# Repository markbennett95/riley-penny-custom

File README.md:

# Custom Dual OD - Riley Penney

Custom dual drive in a 1590BB - Called the "Chinook Overdrive", it features a Zendrive on one side, and a modified BD-2 on the the other.

## v1.0.0-build
1590BB encl. Works with `1590BB-2` of the [Dual Effect Order Switching Board](https://github.com/markbennett95/dual-effect-order-switching-board). Zendrive schematic is unchanged, using the "version" switch and a DG412. The BD-2 is heavily modified from the original; It features an active baxendall 2-band tone stack, and a gyrator-based 3-way "Mids" switch. Some zener diodes were added in the feedback path of the second gain stage, which went a long ways in cleaning up some of the fizziness inherent in the original version.

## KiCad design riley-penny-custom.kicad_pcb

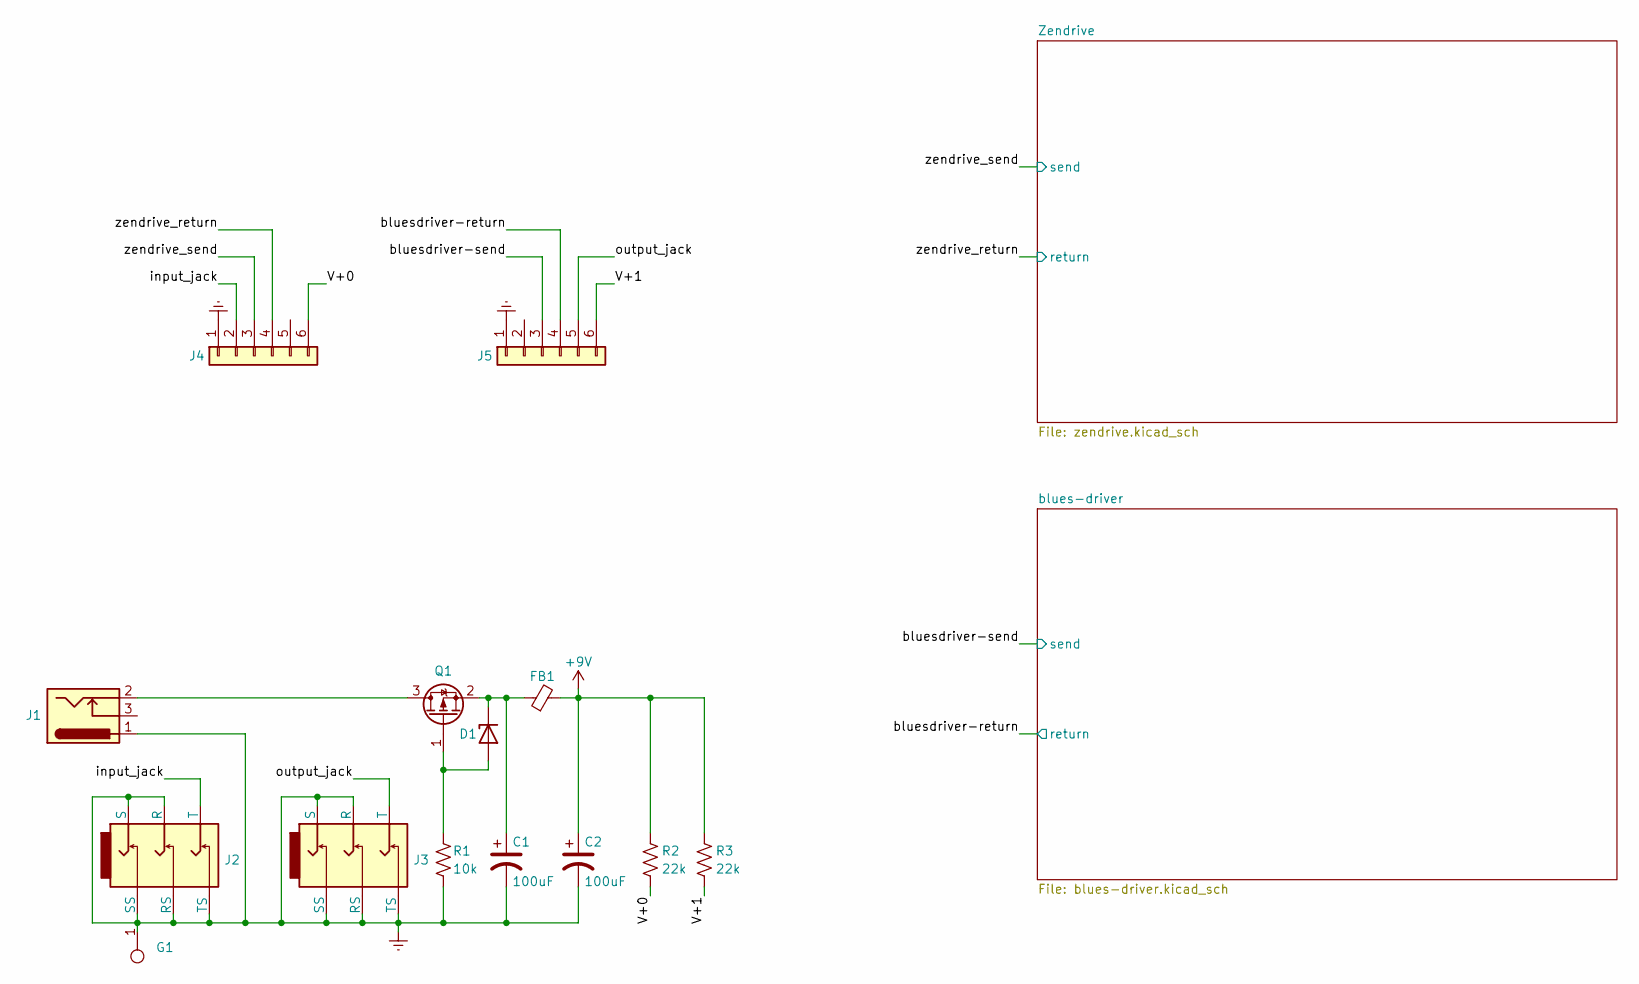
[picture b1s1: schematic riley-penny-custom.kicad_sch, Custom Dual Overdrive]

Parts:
C1, C2: 100uF; CP_Radial_D6.3mm_P2.50mm
D1: 9V1 Zener; D_SOD-323_HandSoldering
FB1: FerriteBead_Small; L_0805_2012Metric_Pad1.15x1.40mm_HandSolder
G1: GNDSpring; Keystone_628
J1: Barrel_Jack_Switch; DC_Jack_DC005
J2, J3: AudioJack_TRS; Rean_NYS215
J4, J5: Conn_01x06; Pin_Header_Straight_1x06_Pitch2.54mm
Q1: Q_PMOS_GSD; SOT-23_Handsoldering
R1: 10k; R_0805_2012Metric_Pad1.20x1.40mm_HandSolder
R2, R3: 22k; R_0805_2012Metric_Pad1.20x1.40mm_HandSolder

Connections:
+9V: C2.1, FB1.2, R2.2, R3.2; also elsewhere on the board
/V+0: J4.6, R2.1
/V+1: J5.6, R3.1
/bluesdriver-return: J5.4; also elsewhere on the board
/bluesdriver-send: J5.3; also elsewhere on the board
/input_jack: J2.1 (T), J4.2
/output_jack: J3.1 (T), J5.5
/zendrive_return: J4.4; also elsewhere on the board
/zendrive_send: J4.3; also elsewhere on the board
Earth: C1.2, C2.2, G1.1, J1.1, J2.2 (R), J2.3 (S), J2.4 (TS), J2.5 (RS), J2.6 (SS), J3.2 (R), J3.3 (S), J3.4 (TS), J3.5 (RS), J3.6 (SS), J4.1, J5.1, R1.1; also elsewhere on the board
unnamed: D1.2 (A), Q1.1 (G), R1.2
unnamed: C1.1, D1.1 (K), FB1.1, Q1.2 (S)
unnamed: J1.2, Q1.3 (D)

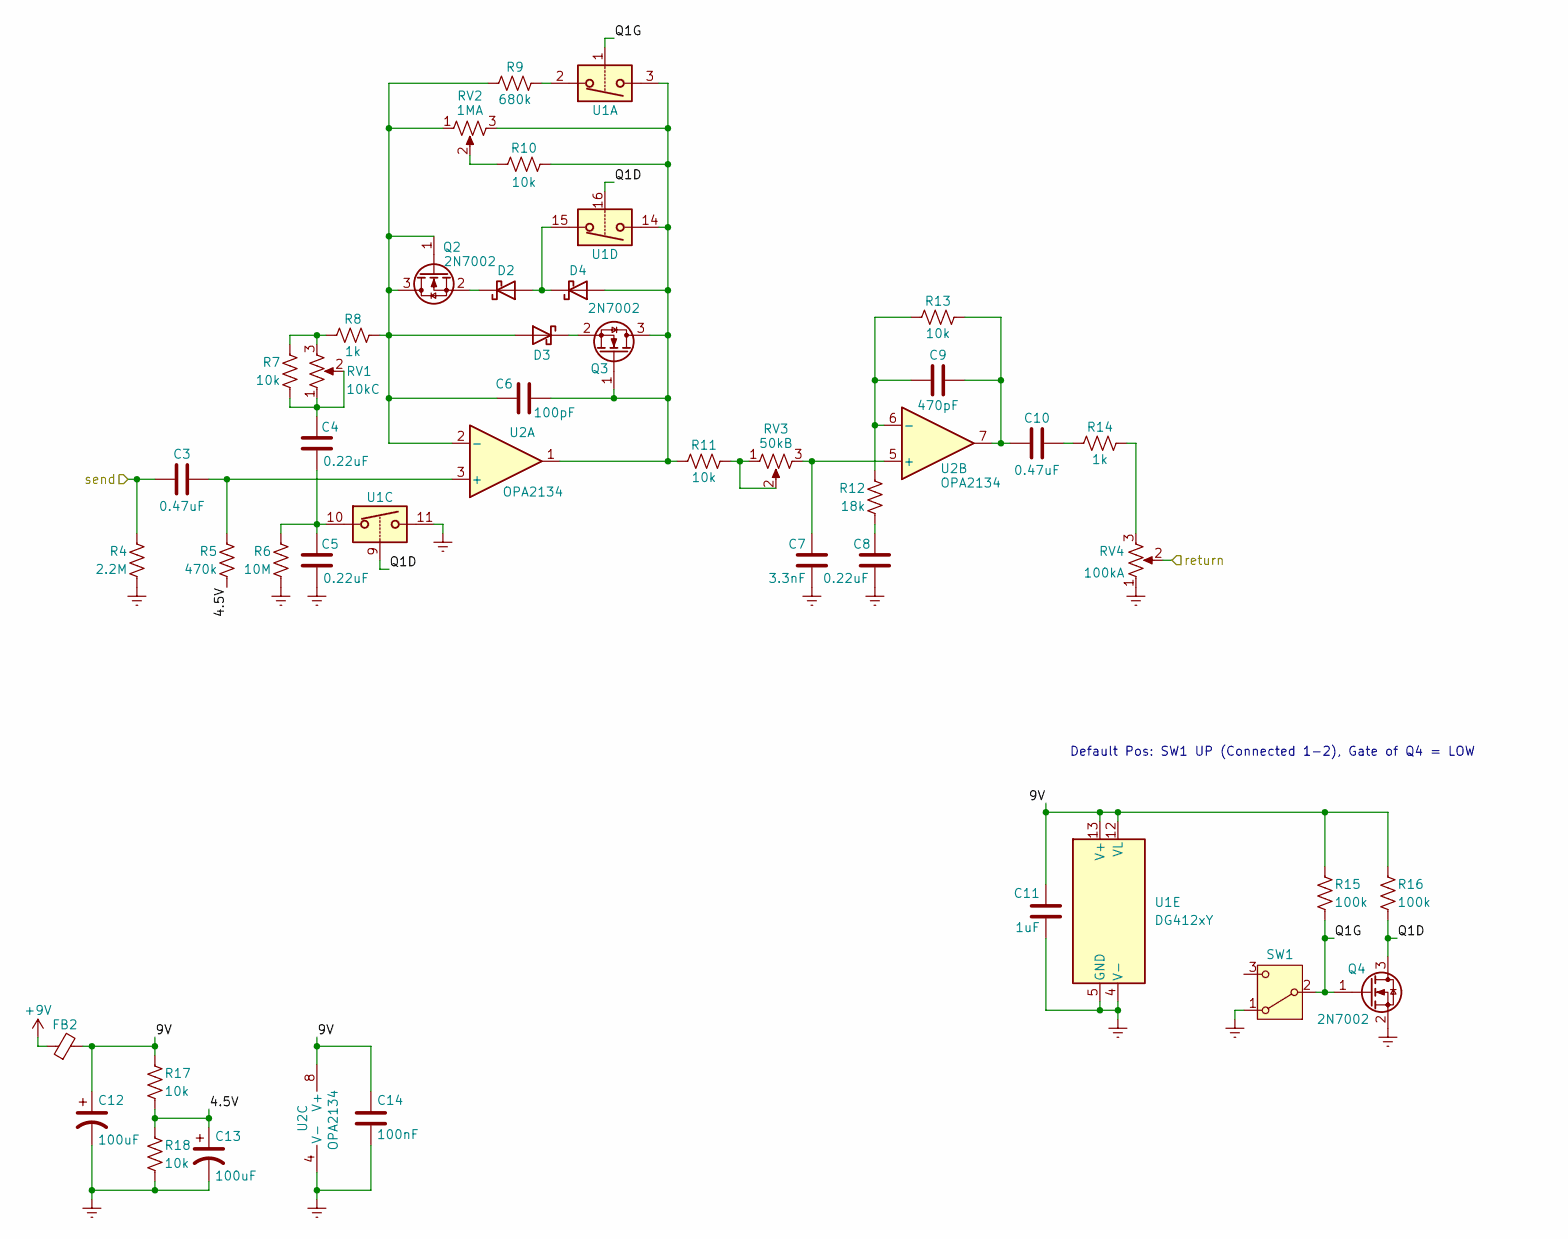
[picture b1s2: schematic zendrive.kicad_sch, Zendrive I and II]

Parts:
C3, C10: 0.47uF; C_Film_L7.2mm_W3.5mm_P5.00mm
C4, C5, C8: 0.22uF; C_Film_L7.2mm_W3.5mm_P5.00mm
C6: 100pF; C_0603_1608Metric_Pad1.08x0.95mm_HandSolder
C7: 3.3nF; C_Film_L7.2mm_W2.5mm_P5.00mm
C9: 470pF; C_0603_1608Metric_Pad1.08x0.95mm_HandSolder
C11: 1uF; C_0805_2012Metric_Pad1.18x1.45mm_HandSolder
C12, C13: 100uF; CP_Radial_D6.3mm_P2.50mm
C14: 100nF; C_0603_1608Metric_Pad1.08x0.95mm_HandSolder
D2, D3, D4: 1N5711; Diode_DO-35_P5.00mm
FB2: FerriteBead_Small; L_0805_2012Metric_Pad1.15x1.40mm_HandSolder
Q2, Q3, Q4: 2N7002; SOT-23_Handsoldering
R4: 2.2M; R_L3.6mm_D1.6mm_P5.00mm_Horizontal
R5: 470k; R_L3.6mm_D1.6mm_P5.00mm_Horizontal
R6: 10M; R_0805_2012Metric_Pad1.20x1.40mm_HandSolder
R7, R10, R11, R13: 10k; R_L3.6mm_D1.6mm_P5.00mm_Horizontal
R8, R14: 1k; R_L3.6mm_D1.6mm_P5.00mm_Horizontal
R9: 680k; R_L3.6mm_D1.6mm_P5.00mm_Horizontal
R12: 18k; R_L3.6mm_D1.6mm_P5.00mm_Horizontal
R15, R16: 100k; R_L3.6mm_D1.6mm_P5.00mm_Horizontal
R17, R18: 10k; R_0805_2012Metric_Pad1.20x1.40mm_HandSolder
RV1: 10kC; R_POT
RV2: 1MA; R_POT
RV3: 50kB; R_POT
RV4: 100kA; R_POT
SW1: SW_SPDT; SW_Toggle_SPDT_SolderLug
U1: DG412xY; SOIC-16_3.9x9.9mm_P1.27mm
U2: OPA2134; SOIC-8_3.9x4.9mm_P1.27mm

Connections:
+9V: FB2.1; also elsewhere on the board
/Zendrive/4.5V: C13.1, R5.1, R17.1, R18.2
/Zendrive/9V: C11.1, C12.1, C14.1, FB2.2, R15.2, R16.2, R17.2, U1.12 (VL), U1.13 (V+), U2.8 (V+)
/Zendrive/Q1D: Q4.3 (D), R16.1, U1.9, U1.16
/Zendrive/Q1G: Q4.1 (G), R15.1, SW1.2 (B), U1.1
/zendrive_return: RV4.2; also elsewhere on the board
/zendrive_send: C3.1, R4.2; also elsewhere on the board
Earth: C5.1, C7.2, C8.1, C11.2, C12.2, C13.2, C14.2, Q4.2 (S), R4.1, R6.1, R18.1, RV4.1, SW1.1 (A), U1.4 (V-), U1.5 (GND), U1.11, U2.4 (V-); also elsewhere on the board
unnamed: C4.1, C5.2, R6.2, U1.10
unnamed: C4.2, R7.1, RV1.1, RV1.2
unnamed: C8.2, R12.1
unnamed: C9.2, C10.1, R13.2, U2.7
unnamed: C10.2, R14.1
unnamed: D2.2 (A), D4.1 (K), U1.15
unnamed: D2.1 (K), Q2.2 (S)
unnamed: C6.1, D3.2 (A), Q2.1 (G), Q2.3 (D), R8.2, R9.1, RV2.1, U2.2 (-)
unnamed: D3.1 (K), Q3.2 (S)
unnamed: C6.2, D4.2 (A), Q3.1 (G), Q3.3 (D), R10.2, R11.1, RV2.3, U1.3, U1.14, U2.1
unnamed: R7.2, R8.1, RV1.3
unnamed: R9.2, U1.2
unnamed: R10.1, RV2.2
unnamed: R11.2, RV3.1, RV3.2
unnamed: R14.2, RV4.3
unnamed: C3.2, R5.2, U2.3 (+)
unnamed: C7.1, RV3.3, U2.5 (+)
unnamed: C9.1, R12.2, R13.1, U2.6 (-)

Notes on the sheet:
Default Pos: SW1 UP (Connected 1-2), Gate of Q4 = LOW

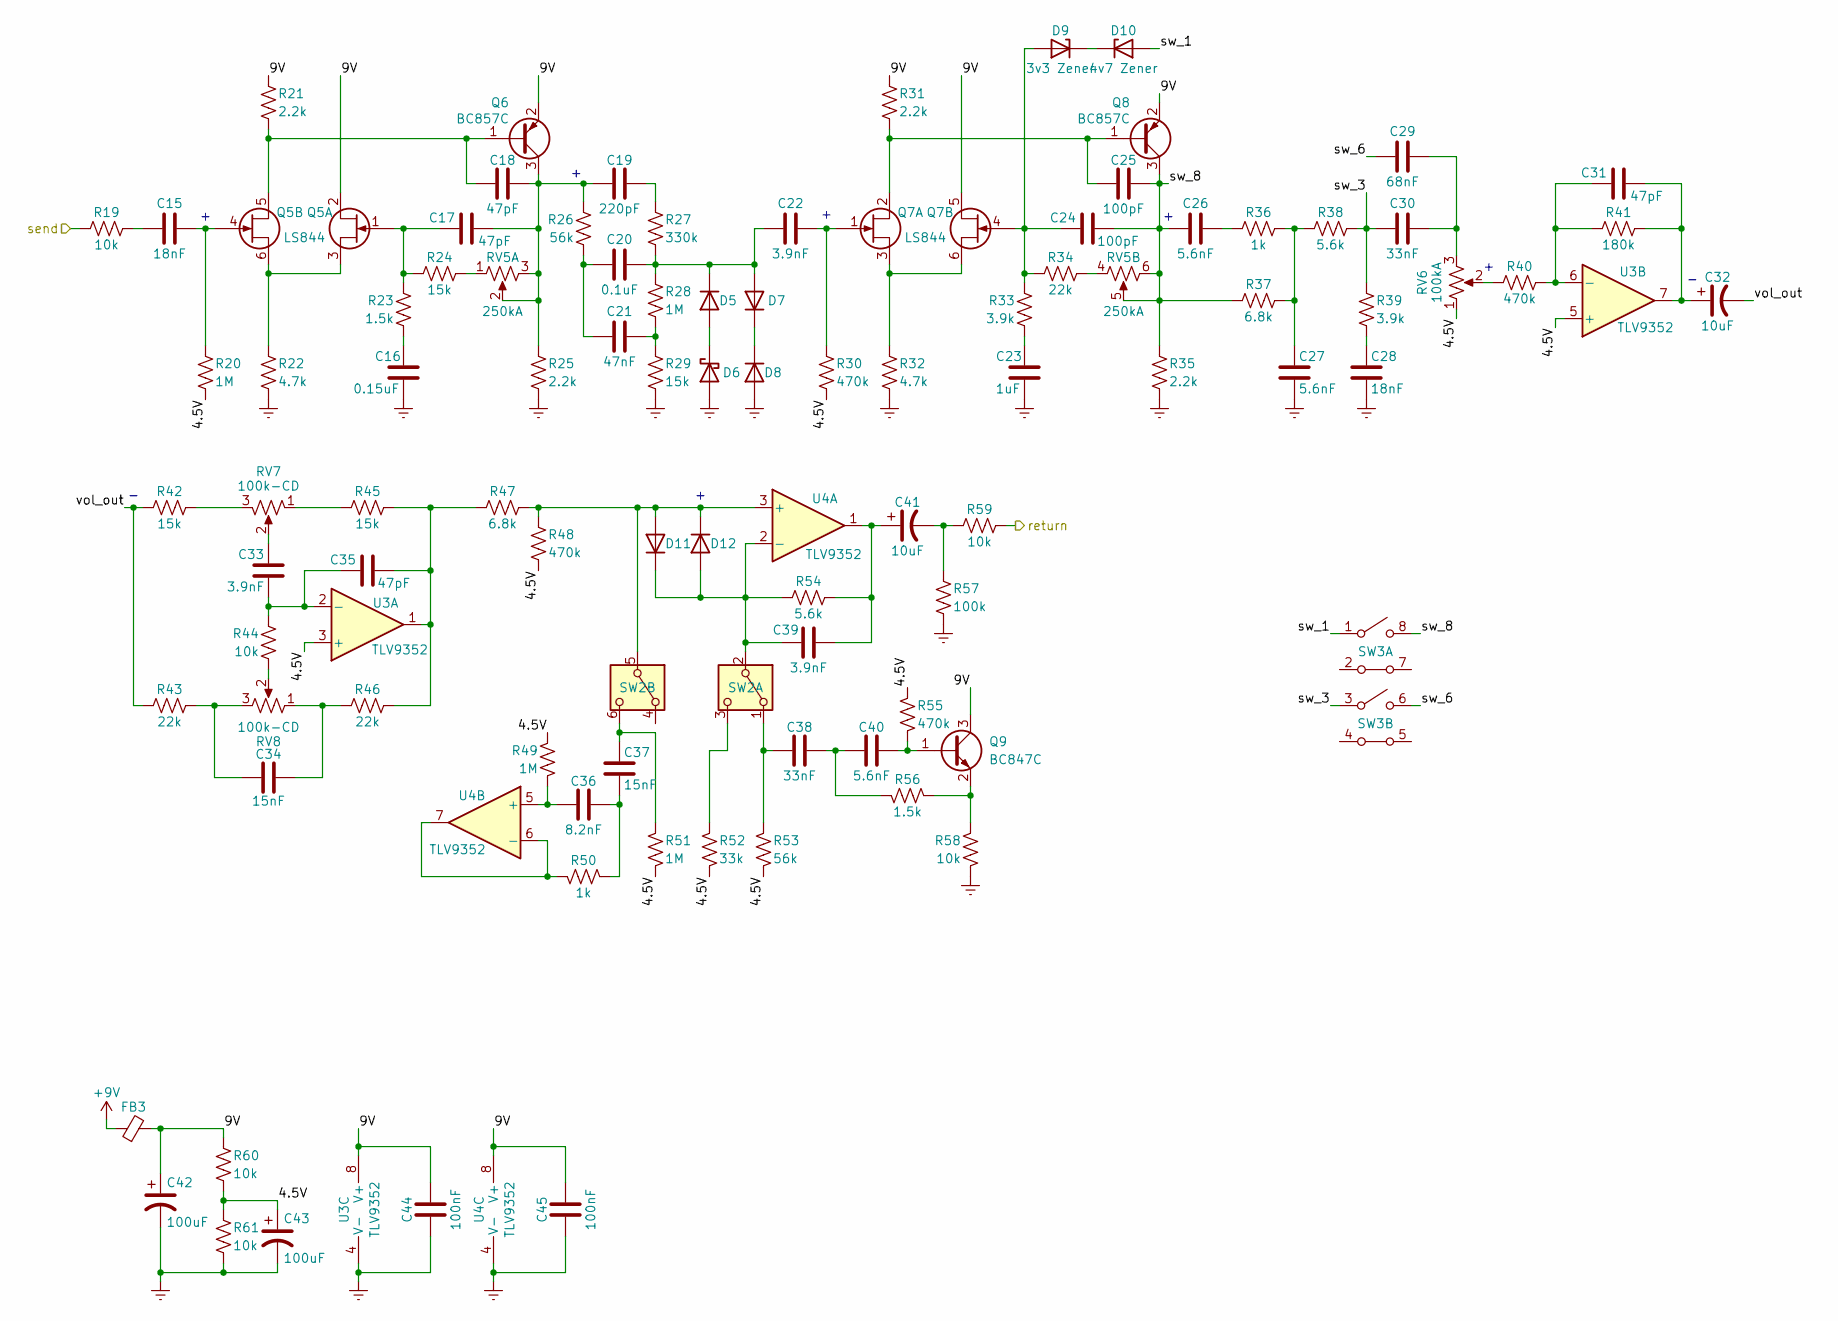
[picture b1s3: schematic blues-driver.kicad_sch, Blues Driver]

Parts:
C15, C28: 18nF; C_Film_L7.2mm_W2.5mm_P5.00mm
C16: 0.15uF; C_Film_L7.2mm_W3.5mm_P5.00mm
C17, C18, C31, C35: 47pF; C_0603_1608Metric_Pad1.08x0.95mm_HandSolder
C19: 220pF; C_Ceramic_L4.0mm_W2.5mm_P2.50mm
C20: 0.1uF; C_Film_L7.2mm_W2.5mm_P5.00mm
C21: 47nF; C_Film_L7.2mm_W2.5mm_P5.00mm
C22, C33, C39: 3.9nF; C_Film_L7.2mm_W2.5mm_P5.00mm
C23: 1uF; C_Film_L7.2mm_W3.5mm_P5.00mm
C24, C25: 100pF; C_0603_1608Metric_Pad1.08x0.95mm_HandSolder
C26, C27, C40: 5.6nF; C_Film_L7.2mm_W2.5mm_P5.00mm
C29: 68nF; C_Film_L7.2mm_W2.5mm_P5.00mm
C30, C38: 33nF; C_Film_L7.2mm_W2.5mm_P5.00mm
C32, C41: 10uF; CP_Radial_D4.0mm_P1.50mm
C34, C37: 15nF; C_Film_L7.2mm_W2.5mm_P5.00mm
C36: 8.2nF; C_Film_L7.2mm_W2.5mm_P5.00mm
C42, C43: 100uF; CP_Radial_D6.3mm_P2.50mm
C44, C45: 100nF; C_0603_1608Metric_Pad1.08x0.95mm_HandSolder
D5, D7, D8, D11, D12: 1N4148; Diode_DO-35_P5.00mm
D6: 1N5711; Diode_DO-35_P5.00mm
D9: 3v3 Zener; Diode_Zener_DO-35_P5.00mm
D10: 4v7 Zener; Diode_Zener_DO-35_P5.00mm
FB3: FerriteBead_Small; L_0805_2012Metric_Pad1.15x1.40mm_HandSolder
Q5, Q7: LS844; SOT-23-6_Handsoldering
Q6, Q8: BC857C; SOT-23_Handsoldering
Q9: BC847C; SOT-23_Handsoldering
R19, R44, R58, R59: 10k; R_L3.6mm_D1.6mm_P5.00mm_Horizontal
R20, R49, R51: 1M; R_0805_2012Metric_Pad1.20x1.40mm_HandSolder
R21, R25, R31, R35: 2.2k; R_0603_1608Metric_Pad0.98x0.95mm_HandSolder
R22, R32: 4.7k; R_0603_1608Metric_Pad0.98x0.95mm_HandSolder
R23, R56: 1.5k; R_L3.6mm_D1.6mm_P5.00mm_Horizontal
R24, R29, R42, R45: 15k; R_L3.6mm_D1.6mm_P5.00mm_Horizontal
R26, R53: 56k; R_L3.6mm_D1.6mm_P5.00mm_Horizontal
R27: 330k; R_L3.6mm_D1.6mm_P5.00mm_Horizontal
R28: 1M; R_L3.6mm_D1.6mm_P5.00mm_Horizontal
R30, R40, R48, R55: 470k; R_L3.6mm_D1.6mm_P5.00mm_Horizontal
R33, R39: 3.9k; R_L3.6mm_D1.6mm_P5.00mm_Horizontal
R34, R43, R46: 22k; R_L3.6mm_D1.6mm_P5.00mm_Horizontal
R36, R50: 1k; R_L3.6mm_D1.6mm_P5.00mm_Horizontal
R37, R47: 6.8k; R_L3.6mm_D1.6mm_P5.00mm_Horizontal
R38, R54: 5.6k; R_L3.6mm_D1.6mm_P5.00mm_Horizontal
R41: 180k; R_L3.6mm_D1.6mm_P5.00mm_Horizontal
R52: 33k; R_0805_2012Metric_Pad1.20x1.40mm_HandSolder
R57: 100k; R_L3.6mm_D1.6mm_P5.00mm_Horizontal
R60, R61: 10k; R_0805_2012Metric_Pad1.20x1.40mm_HandSolder
RV5: 250kA; R_POT_DUAL
RV6: 100kA; R_POT
RV7, RV8: 100k-CD; R_POT
SW2: SW_DPDT_x2; SW_Toggle_DPDT_SolderLug
SW3: SW_DIP_SPDT_2pos; DIP-8_W7.62mm_Socket
U3, U4: TLV9352; SOIC-8_3.9x4.9mm_P1.27mm

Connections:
+9V: FB3.1; also elsewhere on the board
/blues-driver/4.5V: C43.1, R20.1, R30.1, R48.1, R49.2, R51.1, R52.1, R53.1, R55.2, R60.1, R61.2, RV6.1, U3.3 (+), U3.5 (+)
/blues-driver/9V: C42.1, C44.1, C45.1, FB3.2, Q5.2 (D1), Q6.2 (E), Q7.5 (D2), Q8.2 (E), Q9.3 (C), R21.2, R31.2, R60.2, U3.8 (V+), U4.8 (V+)
/blues-driver/sw_1: D10.2 (A), SW3.1 (C)
/blues-driver/sw_3: C30.1, R38.2, R39.2, SW3.3 (C)
/blues-driver/sw_6: C29.1, SW3.6 (A)
/blues-driver/sw_8: C24.2, C25.2, C26.1, Q8.3 (C), R35.2, R37.1, RV5.5, RV5.6, SW3.8 (A)
/blues-driver/vol_out: C32.2, R42.1, R43.1
/bluesdriver-return: R59.2; also elsewhere on the board
/bluesdriver-send: R19.1; also elsewhere on the board
Earth: C16.2, C23.2, C27.1, C28.1, C42.2, C43.2, C44.2, C45.2, D6.2 (A), D8.2 (A), R22.1, R25.1, R29.1, R32.1, R35.1, R57.1, R58.1, R61.1, U3.4 (V-), U4.4 (V-); also elsewhere on the board
unnamed: C15.1, R19.2
unnamed: C16.1, R23.1
unnamed: C19.2, R27.2
unnamed: C20.1, C21.1, R26.1
unnamed: C21.2, R28.1, R29.2
unnamed: C23.1, R33.1
unnamed: C26.2, R36.1
unnamed: C27.2, R36.2, R37.2, R38.1
unnamed: C28.2, R39.1
unnamed: C29.2, C30.2, RV6.3
unnamed: C31.2, C32.1, R41.2, U3.7
unnamed: C33.2, RV7.2
unnamed: C34.1, R46.1, RV8.1
unnamed: C34.2, R43.2, RV8.3
unnamed: C35.2, R45.2, R46.2, R47.1, U3.1
unnamed: C36.2, C37.1, R50.1
unnamed: C38.2, C40.1, R56.2
unnamed: C39.2, C41.1, R54.2, U4.1
unnamed: C41.2, R57.2, R59.1
unnamed: D5.2 (A), D6.1 (K)
unnamed: C20.2, C22.1, D5.1 (K), D7.2 (A), R27.1, R28.2
unnamed: D7.1 (K), D8.1 (K)
unnamed: C24.1, D9.2 (A), Q7.4 (G1), R33.2, R34.1
unnamed: D9.1 (K), D10.1 (K)
unnamed: D11.2 (A), D12.1 (K), R47.2, R48.2, SW2.5 (B), U4.3 (+)
unnamed: C39.1, D11.1 (K), D12.2 (A), R54.1, SW2.2 (B), U4.2 (-)
unnamed: C17.1, Q5.1 (G1), R23.2, R24.1
unnamed: Q5.3 (S1), Q5.6 (S1), R22.2
unnamed: C18.1, Q5.5 (D2), Q6.1 (B), R21.1
unnamed: C15.2, Q5.4 (G1), R20.2
unnamed: C17.2, C18.2, C19.1, Q6.3 (C), R25.2, R26.2, RV5.2 (5), RV5.3 (6)
unnamed: C25.1, Q7.2 (D1), Q8.1 (B), R31.1
unnamed: C22.2, Q7.1 (G1), R30.2
unnamed: Q7.3 (S1), Q7.6 (S1), R32.2
unnamed: C40.2, Q9.1 (B), R55.1
unnamed: Q9.2 (E), R56.1, R58.2
unnamed: R34.2, RV5.4
unnamed: R40.1, RV6.2
unnamed: R42.2, RV7.3
unnamed: R44.1, RV8.2
unnamed: R45.1, RV7.1
unnamed: R24.2, RV5.1 (4)
unnamed: C38.1, R53.2, SW2.1 (A)
unnamed: R52.2, SW2.3 (C)
unnamed: C37.2, R51.2, SW2.6 (C)
unnamed: C33.1, C35.1, R44.2, U3.2 (-)
unnamed: C31.1, R40.2, R41.1, U3.6 (-)
unnamed: C36.1, R49.1, U4.5 (+)
unnamed: R50.2, U4.6 (-), U4.7

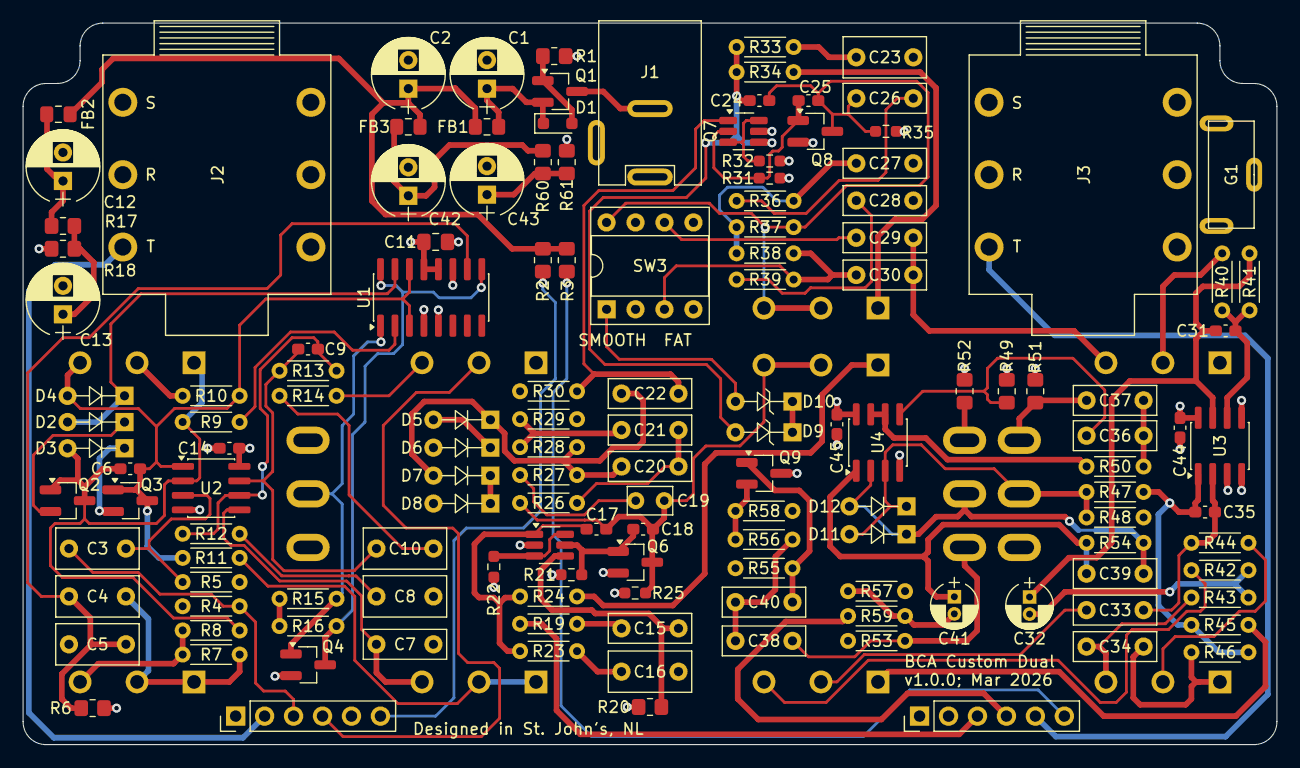
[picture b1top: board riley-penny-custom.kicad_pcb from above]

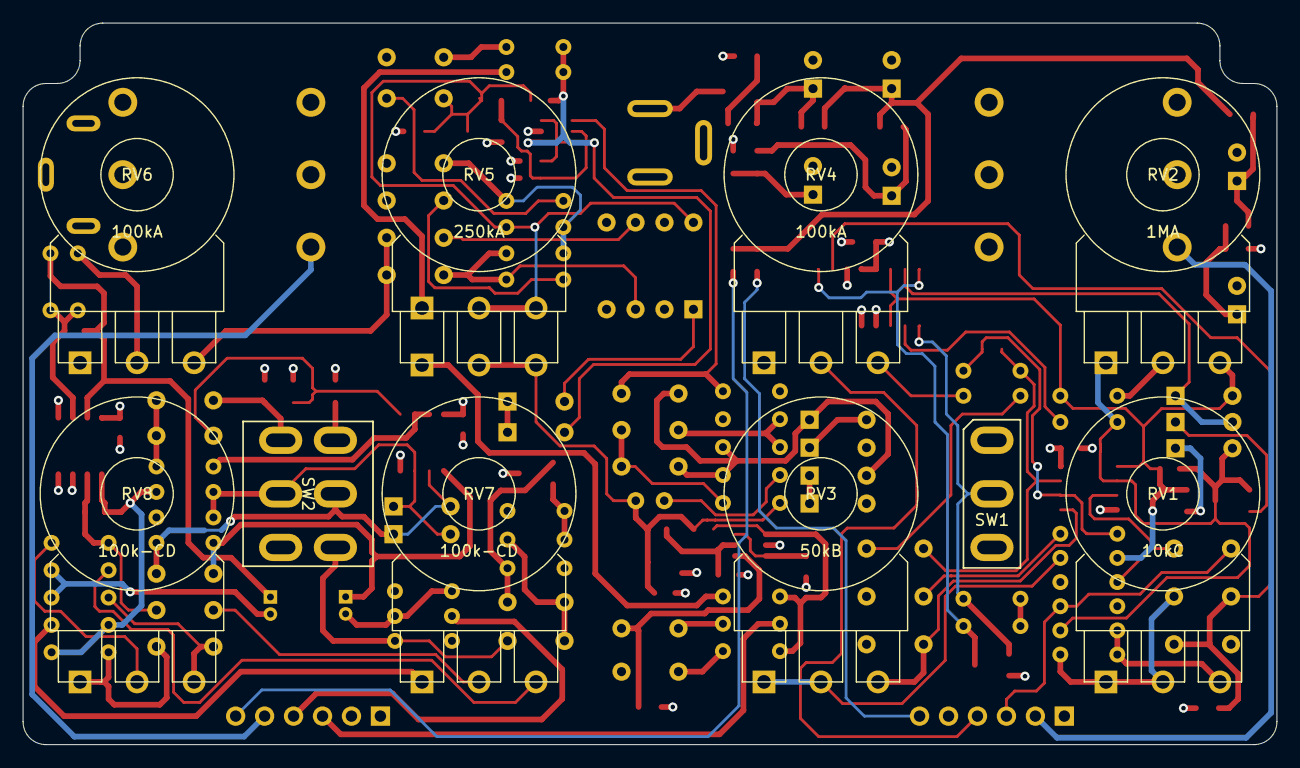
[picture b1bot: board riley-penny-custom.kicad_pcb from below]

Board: 4 copper layers, 110.0 x 63.3 mm, 151 parts (2 on the bottom side), 91 nets.

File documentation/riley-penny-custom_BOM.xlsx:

Value | Qty | Reference | Footprint
2.2k | 4 | R21,R25,R31,R35 | Resistor_SMD:R_0603_1608Metric_Pad0.98x0.95mm_HandSolder
4.7k | 2 | R22,R32 | Resistor_SMD:R_0603_1608Metric_Pad0.98x0.95mm_HandSolder
10k | 5 | R1,R17,R18,R60,R61 | Resistor_SMD:R_0805_2012Metric_Pad1.20x1.40mm_HandSolder
22k | 2 | R2,R3 | Resistor_SMD:R_0805_2012Metric_Pad1.20x1.40mm_HandSolder
33k | 1 | R52 | Resistor_SMD:R_0805_2012Metric_Pad1.20x1.40mm_HandSolder
1M | 3 | R20,R49,R51 | Resistor_SMD:R_0805_2012Metric_Pad1.20x1.40mm_HandSolder
10M | 1 | R6 | Resistor_SMD:R_0805_2012Metric_Pad1.20x1.40mm_HandSolder
47pF | 4 | C17,C18,C31,C35 | Capacitor_SMD:C_0603_1608Metric_Pad1.08x0.95mm_HandSolder
100pF | 3 | C6,C24,C25 | Capacitor_SMD:C_0603_1608Metric_Pad1.08x0.95mm_HandSolder
470pF | 1 | C9 | Capacitor_SMD:C_0603_1608Metric_Pad1.08x0.95mm_HandSolder
100nF | 3 | C14,C44,C45 | Capacitor_SMD:C_0603_1608Metric_Pad1.08x0.95mm_HandSolder
1uF | 1 | C11 | Capacitor_SMD:C_0805_2012Metric_Pad1.18x1.45mm_HandSolder
FerriteBead_Small | 3 | FB1,FB2,FB3 | Inductor_SMD:L_0805_2012Metric_Pad1.15x1.40mm_HandSolder
9V1 Zener | 1 | D1 | Diode_SMD:D_SOD-323_HandSoldering
Q_PMOS_GSD | 1 | Q1 | Package_TO_SOT_SMD:SOT-23_Handsoldering
BC857C | 2 | Q6,Q8 | Package_TO_SOT_SMD:SOT-23_Handsoldering
BC847C | 1 | Q9 | Package_TO_SOT_SMD:SOT-23_Handsoldering
2N7002 | 3 | Q2,Q3,Q4 | Package_TO_SOT_SMD:SOT-23_Handsoldering
LS844 | 2 | Q5,Q7 | Package_TO_SOT_SMD:SOT-23-6_Handsoldering
OPA1642 | 1 | U2 | Package_SO:SOIC-8_3.9x4.9mm_P1.27mm
TLV9352 | 2 | U3,U4 | Package_SO:SOIC-8_3.9x4.9mm_P1.27mm
DG412xY | 1 | U1 | Package_SO:SOIC-16_3.9x9.9mm_P1.27mm
1k | 4 | R8,R14,R36,R50 | bca-footprints:R_L3.6mm_D1.6mm_P5.00mm_Horizontal
1.5k | 2 | R23,R56 | bca-footprints:R_L3.6mm_D1.6mm_P5.00mm_Horizontal
3.9k | 2 | R33,R39 | bca-footprints:R_L3.6mm_D1.6mm_P5.00mm_Horizontal
5.6k | 2 | R38,R54 | bca-footprints:R_L3.6mm_D1.6mm_P5.00mm_Horizontal
6.8k | 3 | R37,R47 | bca-footprints:R_L3.6mm_D1.6mm_P5.00mm_Horizontal
10k | 8 | R7,R10,R11,R13,R19,R44,R58,R59 | bca-footprints:R_L3.6mm_D1.6mm_P5.00mm_Horizontal
15k | 4 | R24,R29,R42,R45 | bca-footprints:R_L3.6mm_D1.6mm_P5.00mm_Horizontal
18k | 1 | R12 | bca-footprints:R_L3.6mm_D1.6mm_P5.00mm_Horizontal
22k | 3 | R34,R43,R46 | bca-footprints:R_L3.6mm_D1.6mm_P5.00mm_Horizontal
56k | 2 | R26,R53 | bca-footprints:R_L3.6mm_D1.6mm_P5.00mm_Horizontal
100k | 3 | R15,R16,R57 | bca-footprints:R_L3.6mm_D1.6mm_P5.00mm_Horizontal
180k | 1 | R41 | bca-footprints:R_L3.6mm_D1.6mm_P5.00mm_Horizontal
330k | 1 | R27 | bca-footprints:R_L3.6mm_D1.6mm_P5.00mm_Horizontal
470k | 5 | R5,R30,R40,R48,R55 | bca-footprints:R_L3.6mm_D1.6mm_P5.00mm_Horizontal
680k | 1 | R9 | bca-footprints:R_L3.6mm_D1.6mm_P5.00mm_Horizontal
1M | 1 | R28 | bca-footprints:R_L3.6mm_D1.6mm_P5.00mm_Horizontal
2.2M | 1 | R4 | bca-footprints:R_L3.6mm_D1.6mm_P5.00mm_Horizontal
1N4148 | 5 | D5,D7,D8,D11,D12 | bca-footprints:Diode_DO-35_P5.00mm
1N5711 | 4 | D2,D3,D4,D6 | bca-footprints:Diode_DO-35_P5.00mm
3v3 Zener | 1 | D9 | bca-footprints:Diode_Zener_DO-35_P5.00mm
4v7 Zener | 1 | D10 | bca-footprints:Diode_Zener_DO-35_P5.00mm
220pF | 1 | C19 | bca-footprints:C_Ceramic_L4.0mm_W2.5mm_P2.50mm
3.3nF | 1 | C7 | bca-footprints:C_Film_L7.2mm_W2.5mm_P5.00mm
3.9nF | 3 | C22,C33,C39 | bca-footprints:C_Film_L7.2mm_W2.5mm_P5.00mm
5.6nF | 3 | C26,C27,C40 | bca-footprints:C_Film_L7.2mm_W2.5mm_P5.00mm
8.2nF | 1 | C36 | bca-footprints:C_Film_L7.2mm_W2.5mm_P5.00mm
15nF | 2 | C34,C37 | bca-footprints:C_Film_L7.2mm_W2.5mm_P5.00mm
18nF | 2 | C15,C28 | bca-footprints:C_Film_L7.2mm_W2.5mm_P5.00mm
33nF | 2 | C30,C38 | bca-footprints:C_Film_L7.2mm_W2.5mm_P5.00mm
47nF | 1 | C21 | bca-footprints:C_Film_L7.2mm_W2.5mm_P5.00mm
68nF | 1 | C29 | bca-footprints:C_Film_L7.2mm_W2.5mm_P5.00mm
0.1uF | 1 | C20 | bca-footprints:C_Film_L7.2mm_W2.5mm_P5.00mm
0.15uF | 1 | C16 | bca-footprints:C_Film_L7.2mm_W3.5mm_P5.00mm
0.22uF | 3 | C4,C5,C8 | bca-footprints:C_Film_L7.2mm_W3.5mm_P5.00mm
0.47uF | 2 | C3,C10 | bca-footprints:C_Film_L7.2mm_W3.5mm_P5.00mm
1uF | 1 | C23 | bca-footprints:C_Film_L7.2mm_W3.5mm_P5.00mm
10uF | 2 | C32,C41 | bca-footprints:CP_Radial_D4.0mm_P1.50mm
100uF | 6 | C1,C2,C12,C13,C42,C43 | bca-footprints:CP_Radial_D6.3mm_P2.50mm
SW_DIP_SPDT_2pos | 1 | SW3 | bca-footprints:DIP-8_W7.62mm_Socket
Barrel_Jack_Switch | 1 | J1 | bca-footprints:DC_Jack_DC005
AudioJack_TRS | 2 | J2,J3 | bca-footprints:Rean_NYS215
GNDSpring | 1 | G1 | bca-footprints:Keystone_628
10kC | 1 | RV1 | bca-footprints:R_POT
50kB | 1 | RV3 | bca-footprints:R_POT
100kA | 2 | RV4,RV6 | bca-footprints:R_POT
100k-CD | 2 | RV7,RV8 | bca-footprints:R_POT
1MA | 1 | RV2 | bca-footprints:R_POT
250kA | 1 | RV5 | bca-footprints:R_POT_DUAL
SW_DPDT_x2 | 1 | SW2 | bca-footprints:SW_Toggle_DPDT_SolderLug
SW_SPDT | 1 | SW1 | bca-footprints:SW_Toggle_SPDT_SolderLug

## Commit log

2026-01-19 renamed files, added schematics
2026-02-16 finished schematics, started PCB
2026-02-17 initial layout
2026-03-06 first draft PCB
2026-03-13 generated production files
2026-04-26 re-generated gerbers, finalized BOM
